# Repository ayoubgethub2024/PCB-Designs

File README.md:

## PCB Specifications

| Parameter | Specification |
|-----------|---------------|
| Microcontroller 1 | ATmega328P (DIP-28 or SMD) |
| Microcontroller 2 | ESP8266 (ESP-12E/F module) |
| Input Voltage | 12-24V DC (industrial standard) |
| Regulated Output | 5V @ 2A, 3.3V @ 800mA |
| Digital Inputs | 6x opto-isolated (24V) |
| Digital Outputs | 4x relay outputs (10A 250VAC) |
| Analog Inputs | 4x (0-5V / 4-20mA selectable) |
| Communication | UART, Modbus RS-485 (optional) |
| PCB Layers | 2-layer |
| PCB Size | 100mm x 80mm |

## Key Components

| Component | Part Number | Function |
|-----------|-------------|----------|
| ATmega328P | ATMEGA328P-PU | Main sensor processor |
| ESP8266 | ESP-12E | WiFi and web server |
| Voltage Regulator | LM2596 | 12V to 5V conversion |
| LDO | AMS1117-3.3 | 5V to 3.3V for ESP |
| Optocoupler | PC817 | Input isolation |
| Relay | SRD-05VDC-SL-C | Output switching |
| RS-485 Transceiver | MAX485 | Modbus communication |

## File Descriptions

| File | Description |
|------|-------------|
| `schematic.pdf` | Complete circuit schematic |
| `pcb_layout.pdf` | PCB layout (top and bottom layers) |
| `gerber_files.zip` | Manufacturing files for PCB fabrication |
| `BOM.csv` | Bill of Materials with part numbers |
| `pcb_render.png` | 3D render of the PCB |

## How to View/Edit

### View Schematics/PCB
1. Download the PDF files
2. Open with any PDF viewer

### Edit (requires EDA software)
- **KiCad** (free, open-source)
- **Altium Designer**
- **EAGLE** (Autodesk)
- **Proteus**

### Order PCBs
1. Download `gerber_files.zip`
2. Upload to PCB manufacturer (JLCPCB, PCBWay, Seeed Studio)
3. Use `BOM.csv` for component procurement

## Production Notes

- 500+ units manufactured and deployed
- Designed for industrial environment (noise immunity, isolation)
- Wide operating temperature range: -20°C to +70°C
- Overvoltage and reverse polarity protection on power input

## Version History

| Version | Date | Changes |
|---------|------|---------|
| v1.0 | 2023 | Initial production release – 500+ units |
| v2.0 | 2024 | Added ESD protection, improved grounding, optional RS-485 |

## Related Repositories

- [ESP8266 Firmware](https://github.com/ayoubgethub2024/embedded-industrial-automation)
- [ATmega328 Firmware](https://github.com/ayoubgethub2024/embedded-industrial-automation/tree/main/atmega328-firmware)
- [PLC Programs](https://github.com/ayoubgethub2024/PLC-industrial-automation)

## Author

Embedded Systems & Industrial Automation Engineer

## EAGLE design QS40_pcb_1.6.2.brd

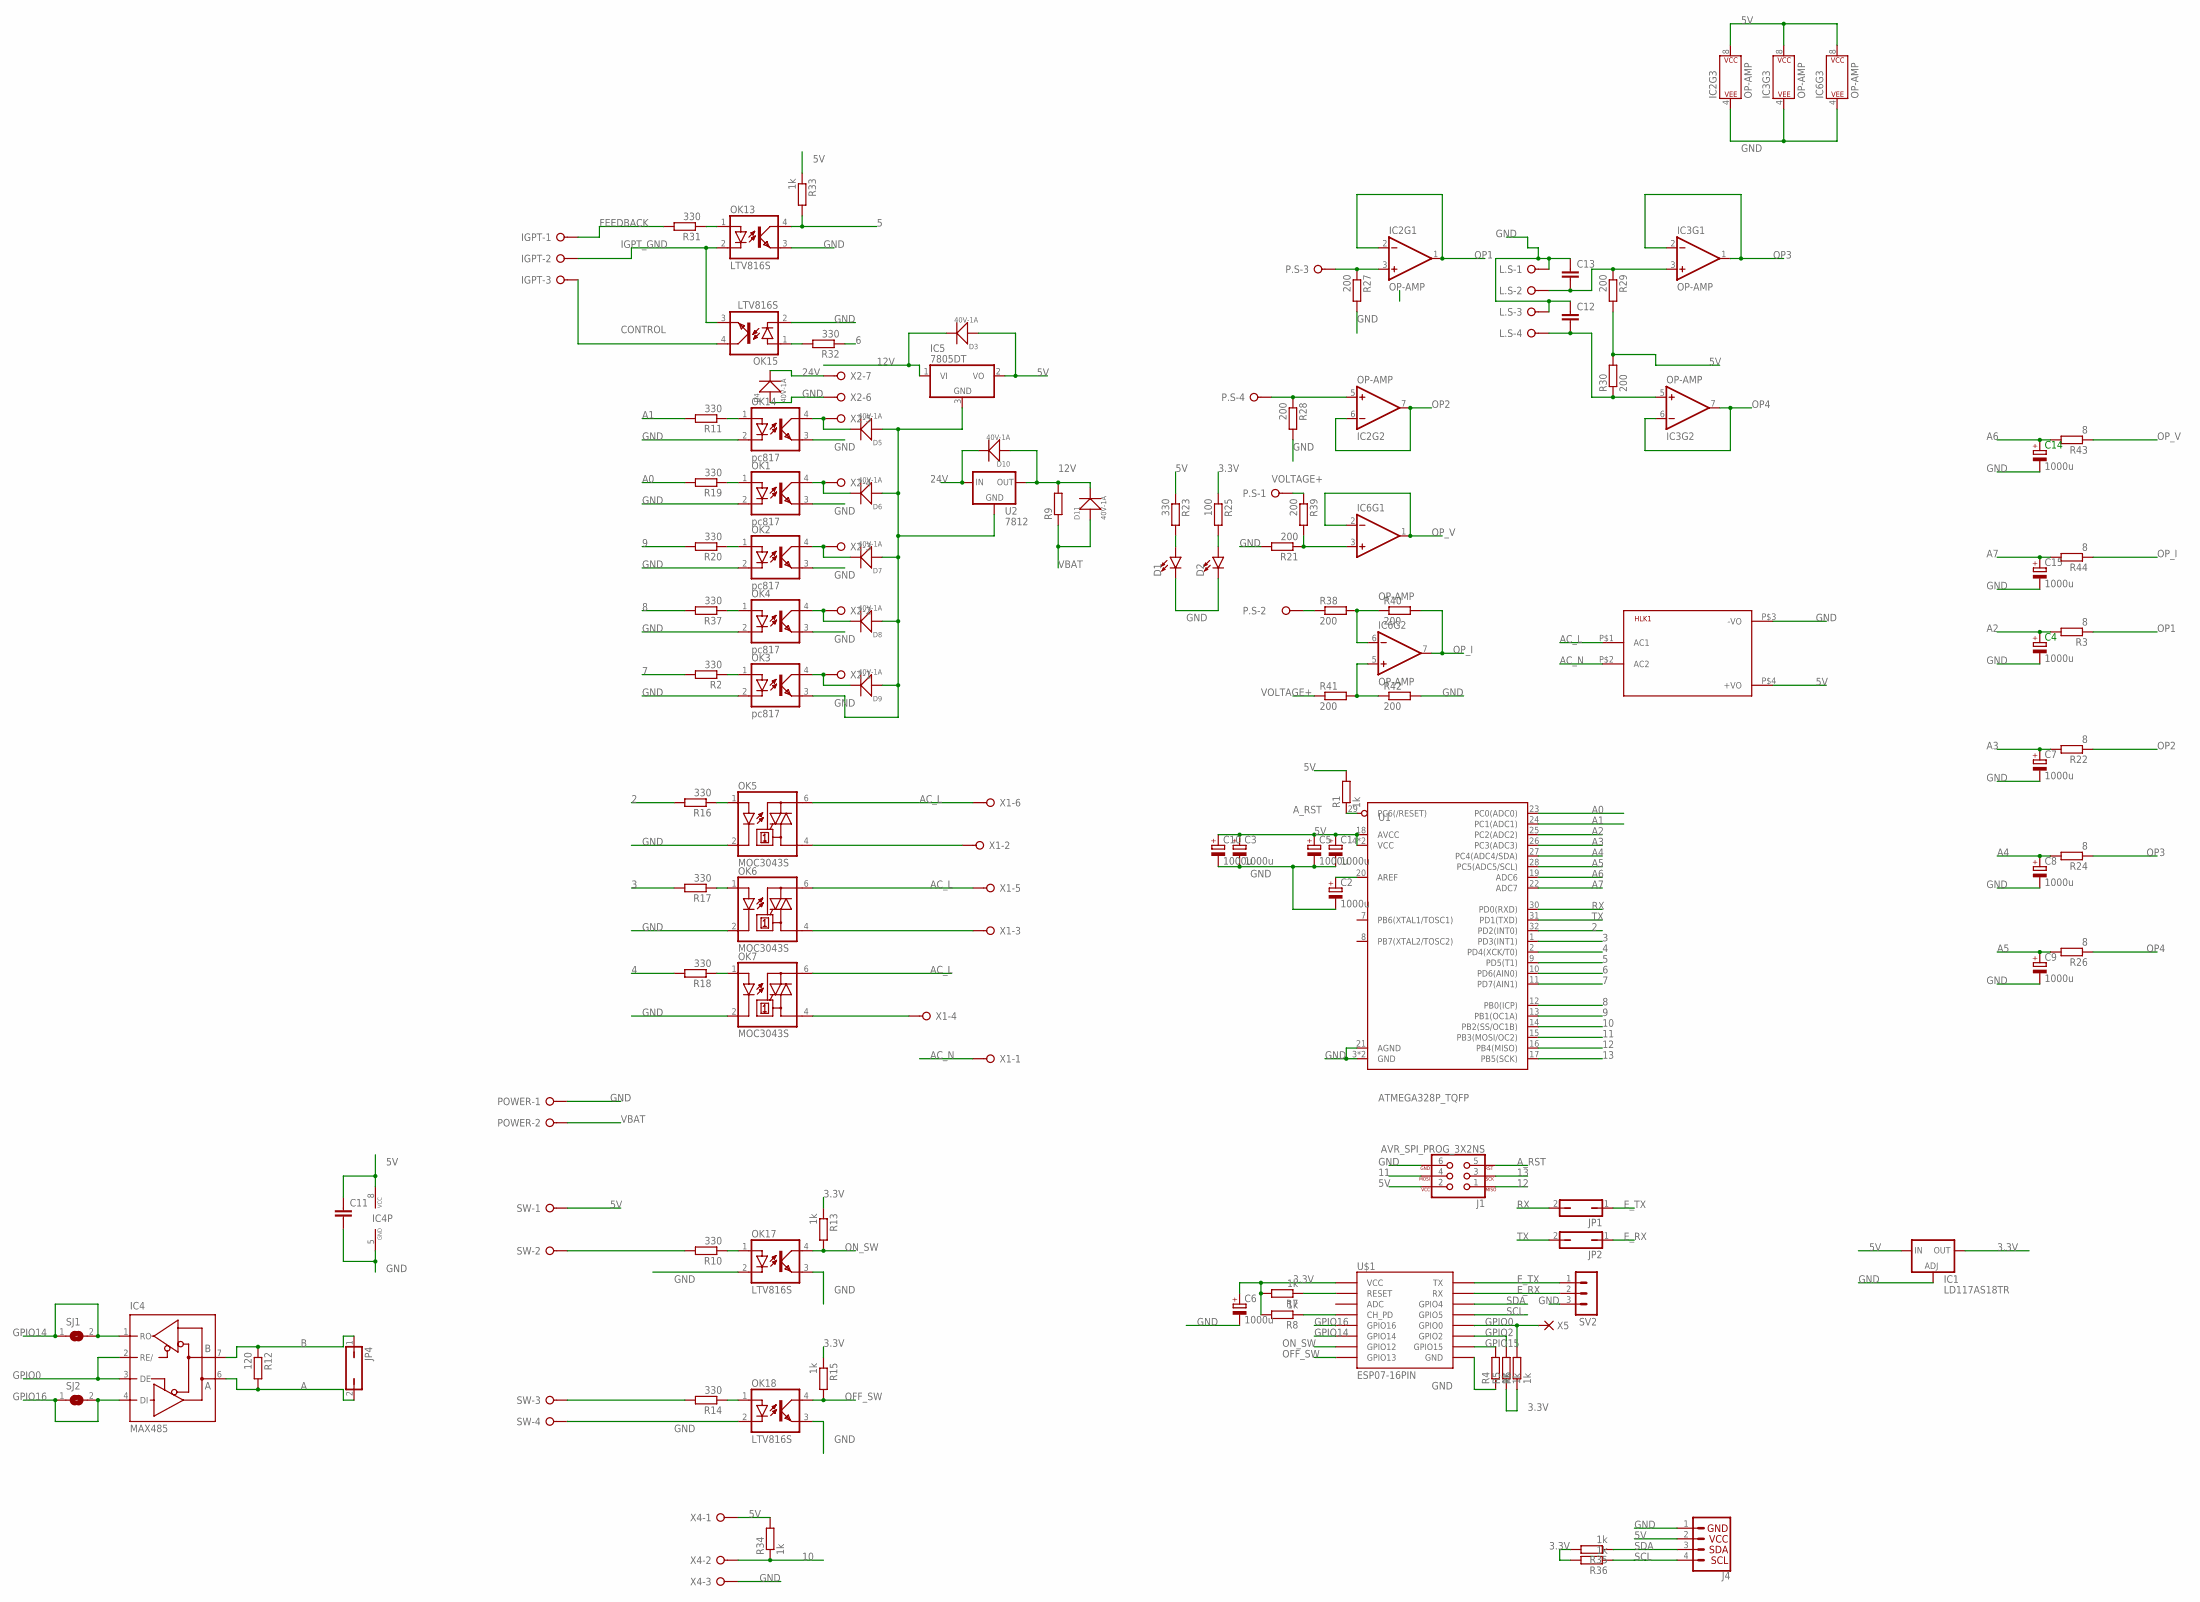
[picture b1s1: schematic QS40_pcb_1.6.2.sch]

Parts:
C1, C2, C3, C4, C5, C6, C7, C8, C9, C10, C14, C15: 1000u; UD-8X10_NICHICON
C11: C-EUC1206K; C1206K
C12, C13: C-EUC1206; C1206
D1, D2: LED-FKIT-1206; FKIT-LED-1206
D3, D4, D5, D6, D7, D8, D9, D10, D11: 40V-1A; DO-214AC
HLK1: HLK-PM013W; HLK-PM01
IC1: LD117AS18TR; SOT223
IC2, IC3, IC6: OP-AMP; SO08
IC4: MAX485; SO08
IC5: 7805DT; TO252
IGPT: W237-03P; W237-133
J1: AVR_SPI_PROG_3X2NS; 2X3-NS
J4: I2C_STANDARD_NO_SILK; 1X04_NO_SILK
JP1, JP2, JP4: JP1Q; JP1
L.S: W237-04P; W237-4P
OK1, OK2, OK3, OK4, OK14: pc817; DIL4-SMD
OK5, OK6, OK7: MOC3043S; DIL6-SMD
OK13, OK15, OK17, OK18: LTV816S; DIL4-SMD
P.S: W237-04P; W237-4P
POWER: W237-02P; W237-132
R1, R4, R5, R6, R7, R8, R13, R15, R33, R34, R35, R36: 1k; R1206W
R2, R10, R11, R14, R16, R17, R18, R19, R20, R23, R31, R32, R37: 330; R1206W
R3, R22, R24, R26, R43, R44: 8; R1206W
R9: R-EU_R5025; R5025
R12: 120; R1206W
R21, R27, R28, R38, R39, R40, R41, R42: 200; R1206
R25: 100; R1206W
R29, R30: 200; R1206W
SJ1, SJ2: SJ
SV2: MA03-1
SW: W237-04P; W237-4P
U1: ATMEGA328P_TQFP; TQFP32-08
U2: 7812; TO-252
U$1: ESP07-16PIN; ESP07
X1: W237-06P; W237-6P
X2: W237-07P; W237-7P
X4: W237-03P; W237-133
X5: PAD-1.00-2.00

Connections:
2: R16.2, U1.32 (PD2(INT0))
3: R17.2, U1.1 (PD3(INT1))
3.3V: C6.+, IC1.4 (OUT), R5.1, R6.1, R7.2, R8.2, R13.1, R15.1, R25.1, R35.2, R36.2, U$1.VCC
4: R18.2, U1.2 (PD4(XCK/T0))
5: OK13.4 (COL), R33.2, U1.9 (PD5(T1))
5V: C1.+, C3.+, C5.+, C10.+, C11.1, D3.1 (+), HLK1.P$4 (+VO), IC1.3 (IN), IC2.8 (P$V+), IC3.8 (P$V+), IC4.8 (VCC), IC5.2 (VO), IC6.8 (P$V+), J1.2, J4.2, R1.2, R23.1, R29.2, R30.2, R33.1, R34.2, SW.1, U1.4 (VCC), U1.6 (VCC), U1.18 (AVCC), X4.1
6: R32.1, U1.10 (PD6(AIN0))
7: R2.2, U1.11 (PD7(AIN1))
8: R37.2, U1.12 (PB0(ICP))
9: R20.2, U1.13 (PB1(OC1A))
10: R34.1, U1.14 (PB2(SS/OC1B)), X4.2
11: J1.4, U1.15 (PB3(MOSI/OC2))
12: J1.1, U1.16 (PB4(MISO))
12V: D3.2 (-), D10.1 (+), D11.2 (-), IC5.1 (VI), R9.2, U2.2 (OUT)
13: J1.3, U1.17 (PB5(SCK))
24V: D4.2 (-), D10.2 (-), U2.1 (IN), X2.7
A: IC4.6 (A), JP4.2, R12.2
A0: R19.2, U1.23 (PC0(ADC0))
A1: R11.2, U1.24 (PC1(ADC1))
A2: C4.+, R3.2, U1.25 (PC2(ADC2))
A3: C7.+, R22.2, U1.26 (PC3(ADC3))
A4: C8.+, R24.2, U1.27 (PC4(ADC4/SDA))
A5: C9.+, R26.2, U1.28 (PC5(ADC5/SCL))
A6: C14.+, R43.2, U1.19 (ADC6)
A7: C15.+, R44.2, U1.22 (ADC7)
AC_L: HLK1.P$1 (AC1), OK5.6 (A2), OK6.6 (A2), OK7.6 (A2), X1.5, X1.6
AC_N: HLK1.P$2 (AC2), X1.1
A_RST: J1.5, R1.1, U1.29 (PC6(/RESET))
B: IC4.7 (B), JP4.1, R12.1
CONTROL: IGPT.3, OK15.4 (COL)
E_RX: JP2.1, SV2.2, U$1.RX
E_TX: JP1.1, SV2.1, U$1.TX
FEEDBACK: IGPT.1, R31.2
GND: C1.-, C2.-, C3.-, C4.-, C5.-, C6.-, C7.-, C8.-, C9.-, C10.-, C11.2, C12.1, C13.1, C14.-, C15.-, D1.C, D2.C, D4.1 (+), D5.1 (+), D6.1 (+), D7.1 (+), D8.1 (+), D9.1 (+), HLK1.P$3 (-VO), IC1.1 (ADJ), IC2.4 (P$V-), IC3.4 (P$V-), IC4.5 (GND), IC5.3 (GND), IC6.4 (P$V-), J1.6, J4.1, L.S.1, L.S.3, OK1.2 (C), OK1.3 (EMIT), OK2.2 (C), OK2.3 (EMIT), OK3.2 (C), OK3.3 (EMIT), OK4.2 (C), OK4.3 (EMIT), OK5.2 (C), OK6.2 (C), OK7.2 (C), OK13.3 (EMIT), OK14.2 (C), OK14.3 (EMIT), OK15.2 (C), OK17.2 (C), OK17.3 (EMIT), OK18.2 (C), OK18.3 (EMIT), POWER.1, R4.1, R21.2, R27.2, R28.2, R42.2, SV2.3, SW.4, U1.3 (GND), U1.5 (GND), U1.21 (AGND), U2.3 (GND), U$1.GND, X2.6, X4.3
GPIO0: IC4.2 (RE/), IC4.3 (DE), R6.2, U$1.GPIO0, X5.1
GPIO2: R5.2, U$1.GPIO2
GPIO14: IC4.1 (RO), SJ1.1, SJ1.2, U$1.GPIO14
GPIO15: R4.2, U$1.GPIO15
GPIO16: IC4.4 (DI), SJ2.1, SJ2.2, U$1.GPIO16
IGPT_GND: IGPT.2, OK13.2 (C), OK15.3 (EMIT)
unnamed: OK5.4 (A1), X1.2
unnamed: IC2.3 (+IN), P.S.3, R27.1
unnamed: R7.1, U$1.REST (RESET)
unnamed: R8.1, U$1.CH_PD
unnamed: C2.+, U1.20 (AREF)
unnamed: OK7.4 (A1), X1.4
unnamed: OK14.1 (A), R11.1
unnamed: OK3.1 (A), R2.1
unnamed: OK1.1 (A), R19.1
unnamed: OK6.4 (A1), X1.3
unnamed: OK2.1 (A), R20.1
unnamed: OK4.1 (A), R37.1
unnamed: C13.2, IC3.3 (+IN), L.S.2, R29.1
unnamed: D1.A, R23.2
unnamed: D2.A, R25.2
unnamed: D5.2 (-), OK14.4 (COL), X2.5
unnamed: D6.2 (-), OK1.4 (COL), X2.4
unnamed: D7.2 (-), OK2.4 (COL), X2.3
unnamed: C12.2, IC3.5 (+IN), L.S.4, R30.1
unnamed: OK15.1 (A), R32.2
unnamed: IC2.5 (+IN), P.S.4, R28.1
unnamed: D8.2 (-), OK4.4 (COL), X2.2
unnamed: D9.2 (-), OK3.4 (COL), X2.1
unnamed: OK17.1 (A), R10.1
unnamed: P.S.2, R38.1
unnamed: OK5.1 (A), R16.1
unnamed: R10.2, SW.2
unnamed: OK18.1 (A), R14.1
unnamed: IC6.5 (+IN), R41.2, R42.1
unnamed: IC6.3 (+IN), R21.1, R39.2
unnamed: OK6.1 (A), R17.1
unnamed: IC6.6 (-IN), R38.2, R40.1
unnamed: R14.2, SW.3
unnamed: OK7.1 (A), R18.1
unnamed: OK13.1 (A), R31.1
OFF_SW: OK18.4 (COL), R15.2, U$1.GPIO13
ON_SW: OK17.4 (COL), R13.2, U$1.GPIO12
OP1: IC2.1 (OUT), IC2.2 (-IN), R3.1
OP2: IC2.6 (-IN), IC2.7 (OUT), R22.1
OP3: IC3.1 (OUT), IC3.2 (-IN), R24.1
OP4: IC3.6 (-IN), IC3.7 (OUT), R26.1
OP_I: IC6.7 (OUT), R40.2, R44.1
OP_V: IC6.1 (OUT), IC6.2 (-IN), R43.1
RX: JP1.2, U1.30 (PD0(RXD))
SCL: J4.4, R36.1, U$1.GPIO5
SDA: J4.3, R35.1, U$1.GPIO4
TX: JP2.2, U1.31 (PD1(TXD))
VBAT: D11.1 (+), POWER.2, R9.1
VOLTAGE+: P.S.1, R39.1, R41.1

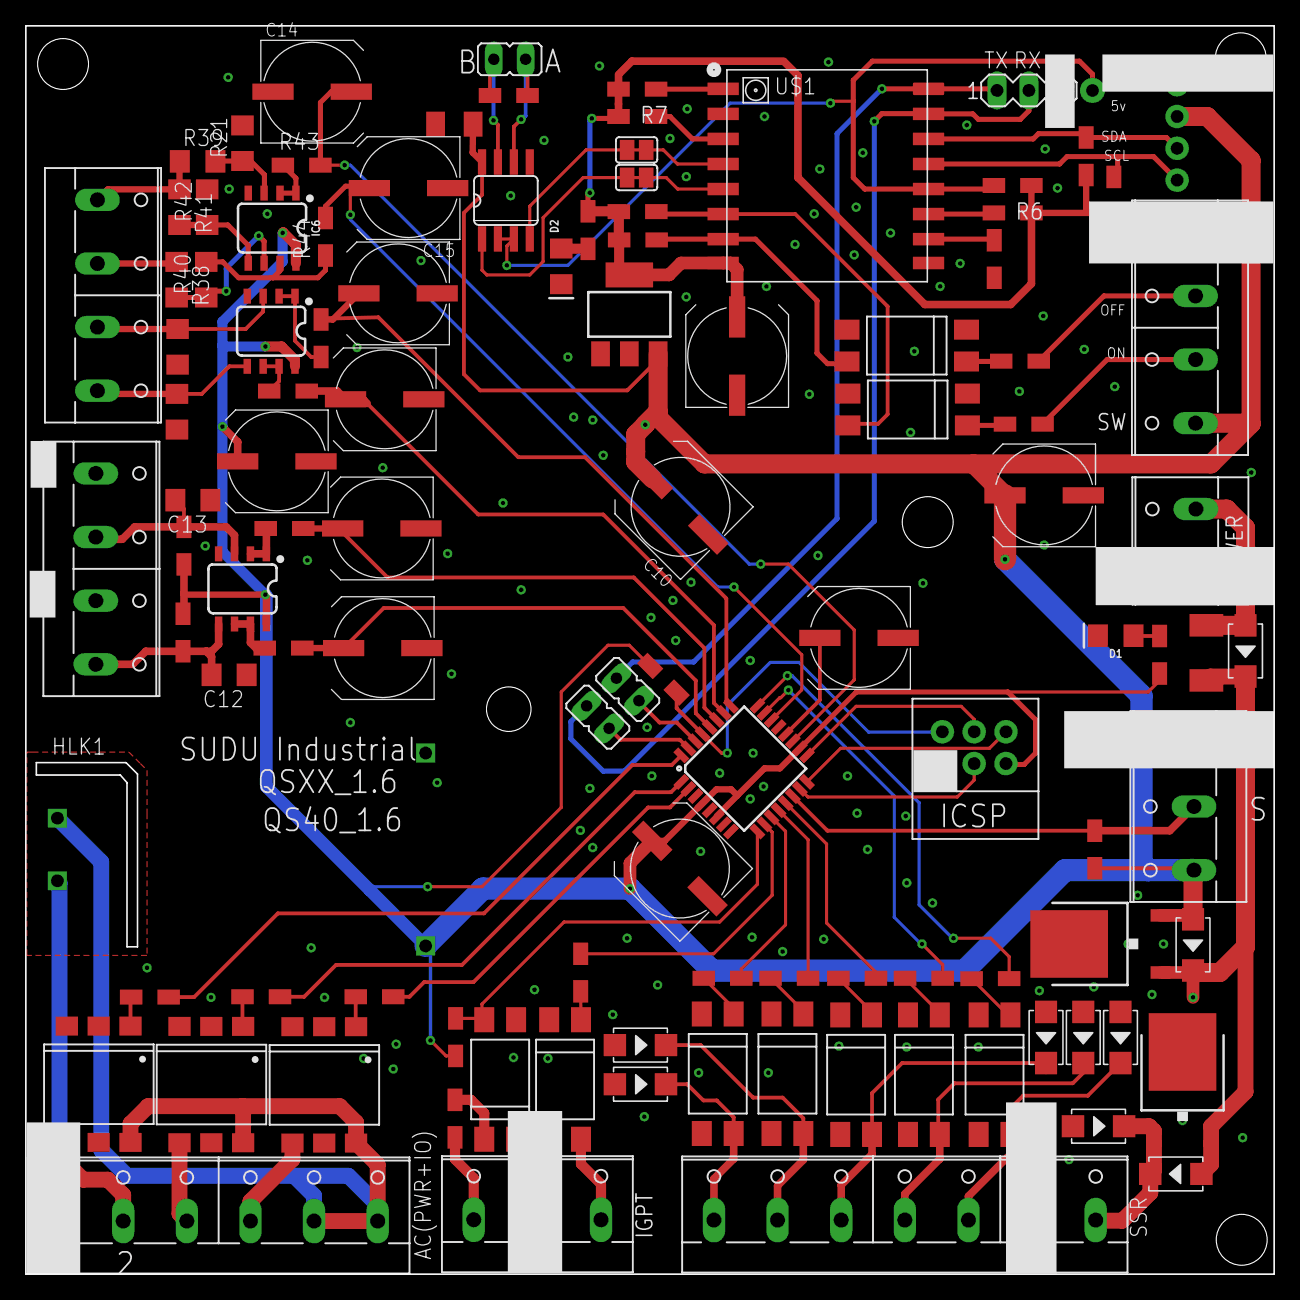
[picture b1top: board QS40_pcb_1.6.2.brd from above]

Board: 2 copper layers, 99.7 x 99.7 mm, 109 parts (0 on the bottom side), 89 nets.

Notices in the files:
parts and their libraries:
SparkFun-RF: Licensing: Creative Commons ShareAlike 4.0 International - https://creativecommons.org/licenses/by-sa/4.0
